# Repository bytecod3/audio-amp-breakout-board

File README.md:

## Class AB Audio Amplifier With TDA2030
### Introduction
The amplifier shown below uses the very versatile monolithic IC TDA2030 audio amplifier
to amplify the audio input from a 3.5mm Jack to power a subwoofer. It delivers an
output of 12W for 4 Ohm speaker and 8W for a 8 Ohm speaker.

### Schematic

From the AUDIO_IN input, RV1 is a volume control knob. The amplifier is DC coupled
with C1. C1 and R1 form a high pass filter network to allow high freq signals
to be amplified.

TDA2030 is powered with 12V VCC. The 1N4001 Diode is a reverse protection component
to prevent the capacitors CP1 and C3 from getting damaged. R2 is a potential divider to bias the IC.

CP1, C3 and C2 are noise filters. 

The gain for this circuit is set by R5 and R4 and is given by: -R5/R4, which in this
case gives 25.6 dB. 

The series network formed by R7 and C4 is a Zobel network used to correct some of the 
internal amplifier inefficiencies. 

### Layout  

There are ground copper fills on both the front and back copper sides to drive the 
noise to ground and prevent background hissing

### 3D view

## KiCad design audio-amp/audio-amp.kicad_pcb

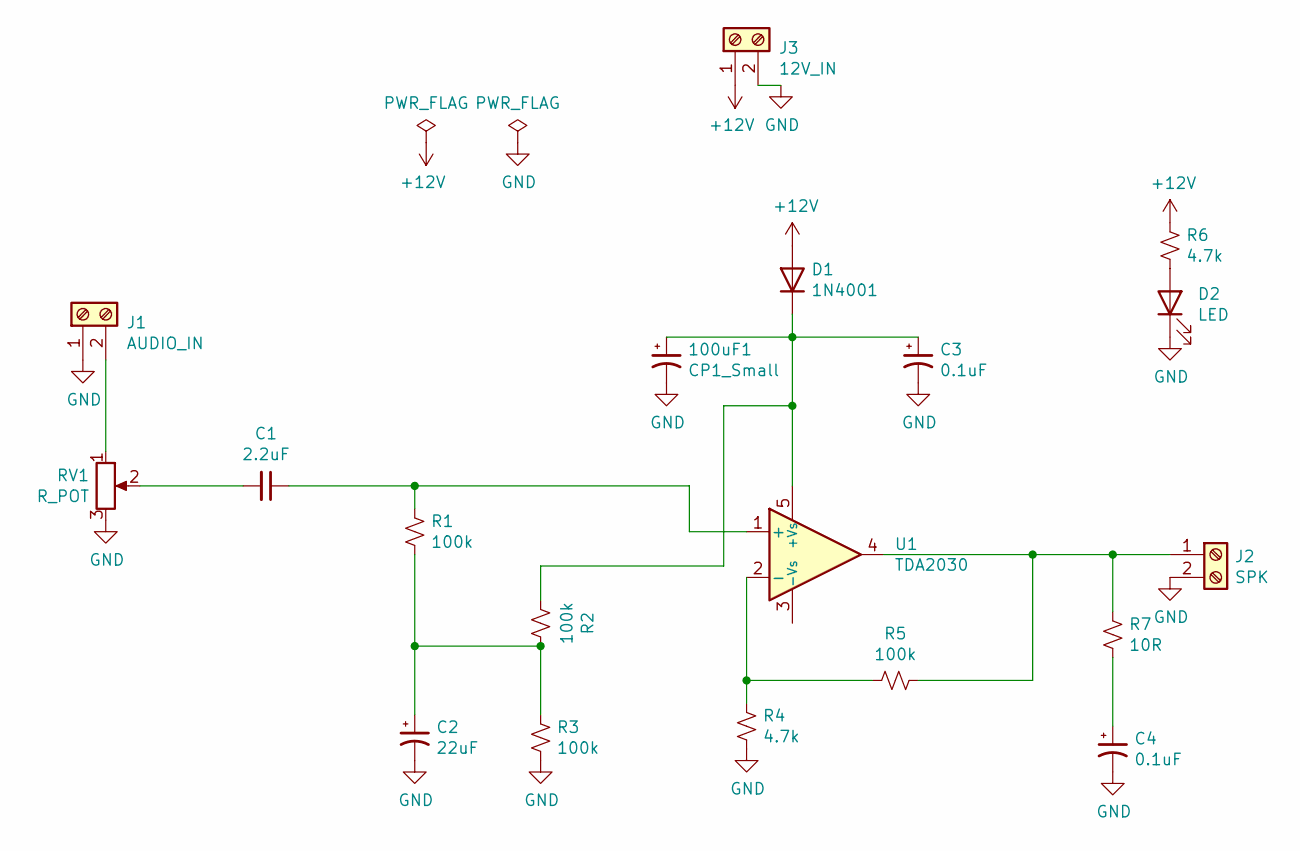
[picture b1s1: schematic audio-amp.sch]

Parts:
100uF1: CP1_Small; CP_Radial_D4.0mm_P2.00mm
C1: 2.2uF; CP_Radial_D4.0mm_P2.00mm
C2: 22uF; CP_Radial_D4.0mm_P2.00mm
C3, C4: 0.1uF; CP_Radial_D4.0mm_P2.00mm
D1: 1N4001; D_DO-34_SOD68_P7.62mm_Horizontal
D2: LED; LED_D3.0mm
J1: AUDIO_IN; JST_EH_B2B-EH-A_1x02_P2.50mm_Vertical
J2: SPK; JST_EH_B2B-EH-A_1x02_P2.50mm_Vertical
J3: 12V_IN; JST_EH_B2B-EH-A_1x02_P2.50mm_Vertical
R1, R2, R3, R5: 100k; R_Axial_DIN0204_L3.6mm_D1.6mm_P7.62mm_Horizontal
R4, R6: 4.7k; R_Axial_DIN0204_L3.6mm_D1.6mm_P7.62mm_Horizontal
R7: 10R; R_Axial_DIN0204_L3.6mm_D1.6mm_P7.62mm_Horizontal
RV1: R_POT; Potentiometer_Alps_RK09Y11_Single_Horizontal
U1: TDA2030; TO-220-5_P3.4x3.7mm_StaggerOdd_Lead3.8mm_Vertical

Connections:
+12V: D1.2 (A), J3.1, R6.2
GND: 100uF1.2, C2.2, C3.2, C4.2, D2.1 (K), J1.1, J2.2, J3.2, R3.1, R4.1, RV1.3
unnamed: 100uF1.1, C3.1, D1.1 (K), R2.2, U1.5 (+Vs)
unnamed: C1.1, R1.2, U1.1 (+)
unnamed: C1.2, RV1.2
unnamed: C2.1, R1.1, R2.1, R3.2
unnamed: C4.1, R7.1
unnamed: D2.2 (A), R6.1
unnamed: J1.2, RV1.1
unnamed: J2.1, R5.1, R7.2, U1.4
unnamed: R4.2, R5.2, U1.2 (-)

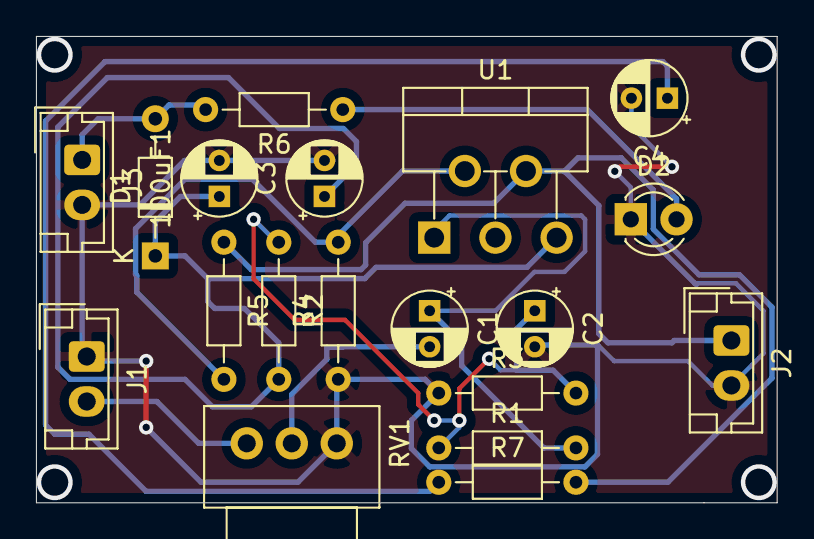
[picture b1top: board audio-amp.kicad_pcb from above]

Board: 2 copper layers, 41.1 x 25.9 mm, 19 parts (0 on the bottom side), 11 nets.

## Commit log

2021-09-02 add copper zones
